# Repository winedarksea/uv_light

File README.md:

# uv_light
Licence: CERN Open Hardware Licence Version 2 - Strongly Reciprocal

 Custom Sun Lamp / Full Spectrum Lamp
 
 Background writeup [here](https://syllepsis.live/2024/12/31/light-for-health-and-a-custom-sun-lamp/)

A heatsink is important. All 16 leds are too much, unfortunately.

Problem: the comparator circuit for voltage sensing doesn't work properly, and needs a look at.

Minor problem: there's one trace that is bridged by the heatsink here. Using a non conductive thermal pad between the pcb and heatsink solves that problem, or redesign.

Recommendation: add a switch to the UV circuit as well. Also perhaps use larger switches than those specced here if you intend to switch the active lights often.

Designed for:
* QLUV07EYGE
* JE2835 3V N CLASS FAR RED
* Samsung LM302N White, Cool 6500K 
* Samsung LM302N WARM WHT 2700K 1212
* GT PSLR31.13-LUMQ-T1T2-1-150-R18 LED DURIS S5 GREEN 540NM SMD

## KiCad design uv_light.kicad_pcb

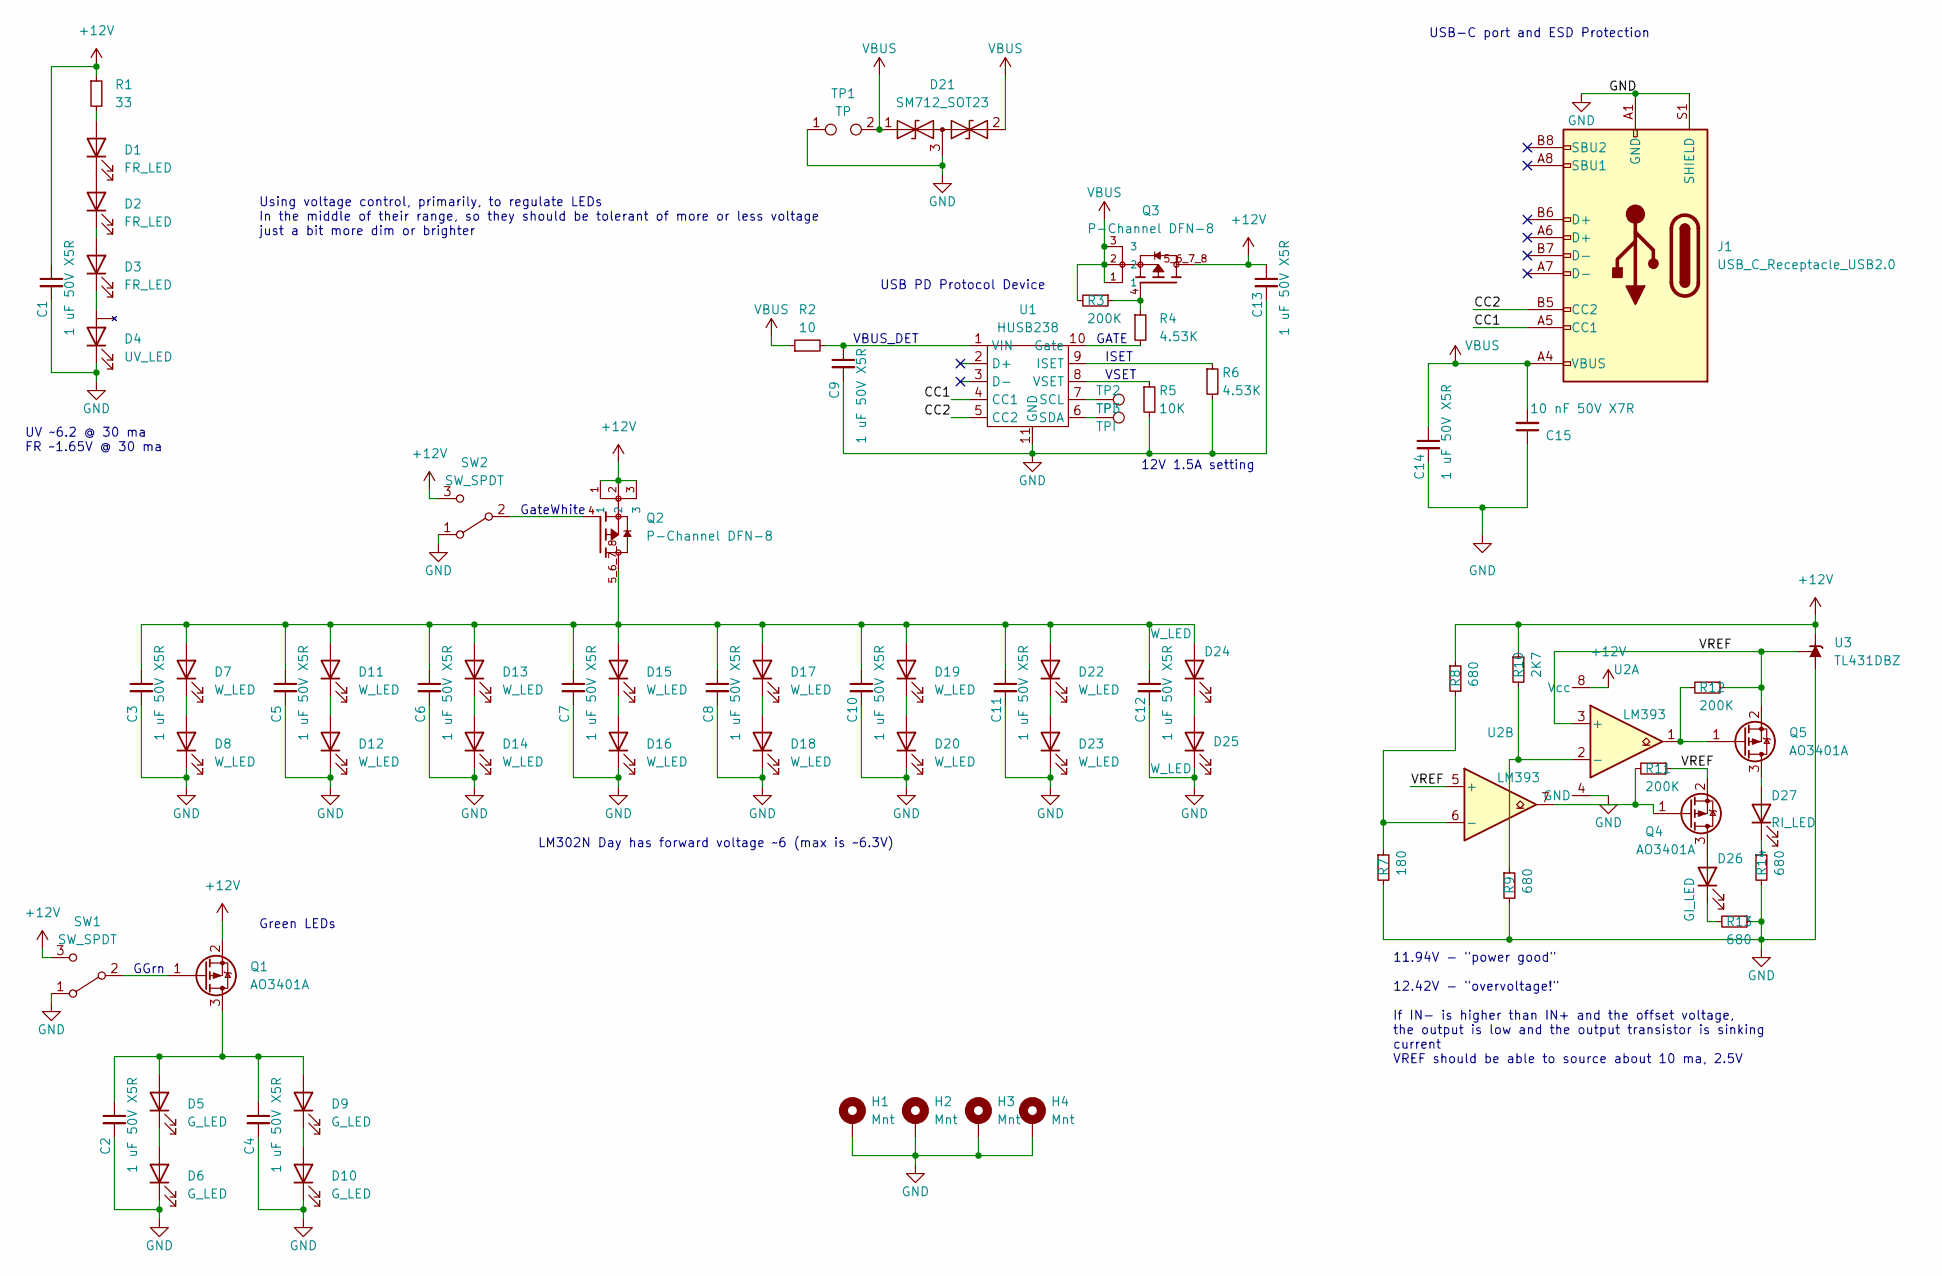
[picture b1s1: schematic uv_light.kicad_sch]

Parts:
C1, C2, C3, C4, C5, C6, C7, C8, C9, C10, C11, C12, C13, C14: 1 uF 50V X5R; C_0603_1608Metric
C15: 10 nF 50V X7R; C_0402_1005Metric_Pad0.74x0.62mm_HandSolder
D1, D2, D3: FR_LED; LED_PLCC_2835_Handsoldering
D4: UV_LED; LED_Cree-XHP35
D5, D6, D9, D10: G_LED; LED_SMD3030
D7, D8, D11, D12, D13, D14, D15, D16, D17, D18, D19, D20, D22, D23, D24, D25: W_LED; LED_SMD3030
D21: SM712_SOT23; SOT-23
D26: GI_LED; LED_0805_2012Metric_Pad1.15x1.40mm_HandSolder
D27: RI_LED; LED_0603_1608Metric_Pad1.05x0.95mm_HandSolder
H1, H2, H3, H4: Mnt; MountingHole_2.2mm_M2_DIN965_Pad
J1: USB_C_Receptacle_USB2.0; USB_C_Receptacle_HRO_TYPE-C-31-M-12
Q1, Q4, Q5: AO3401A; SOT-23
Q2, Q3: P-Channel DFN-8; TRANS_AONR21307
R1: 33; R_0603_1608Metric_Pad0.98x0.95mm_HandSolder
R2: 10; R_0805_2012Metric_Pad1.20x1.40mm_HandSolder
R3, R11, R12: 200K; R_0402_1005Metric_Pad0.72x0.64mm_HandSolder
R4, R6: 4.53K; R_0603_1608Metric_Pad0.98x0.95mm_HandSolder
R5: 10K; R_0603_1608Metric_Pad0.98x0.95mm_HandSolder
R7: 180; R_0603_1608Metric_Pad0.98x0.95mm_HandSolder
R8, R9, R13, R14: 680; R_0805_2012Metric_Pad1.20x1.40mm_HandSolder
R10: 2K7; R_0603_1608Metric_Pad0.98x0.95mm_HandSolder
SW1, SW2: SW_SPDT; SW_SPDT_PCM12
TP1: TP; TestPoint_2Pads_Pitch2.54mm_Drill0.8mm
TP2, TP3: TPI; TestPoint_Pad_D2.0mm
U1: HUSB238; DFN-10-1EP_3x3mm_P0.5mm_EP1.65x2.38mm
U2: LM393; SOIC-8_3.9x4.9mm_P1.27mm
U3: TL431DBZ; SOT-23

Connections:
+12V: C1.1, C13.1, Q1.2 (S), Q2.1, Q2.2, Q2.3, Q3.5_6_7_8, R1.1, R8.1, R10.1, SW1.3 (C), SW2.3 (C), U2.8 (Vcc), U3.1 (K)
/CC1: J1.A5 (CC1), U1.4 (CC1)
/CC2: J1.B5 (CC2), U1.5 (CC2)
/VREF: Q4.2 (S), Q5.2 (S), R11.1, R12.1, U2.3 (+), U2.5 (+), U3.2 (REF)
GND: C1.2, C2.2, C3.2, C4.2, C5.2, C6.2, C7.2, C8.2, C9.2, C10.2, C11.2, C12.2, C13.2, C14.2, C15.1, D4.1 (K), D6.1 (K), D8.1 (K), D10.1 (K), D12.1 (K), D14.1 (K), D16.1 (K), D18.1 (K), D20.1 (K), D21.3 (common), D23.1 (K), D25.1 (K), H1.1, H2.1, H3.1, H4.1, J1.A1 (GND), J1.A12 (GND), J1.B1 (GND), J1.B12 (GND), J1.S1 (SHIELD), R5.2, R6.2, R7.2, R9.2, R13.1, R14.2, SW1.1 (A), SW2.1 (A), TP1.1, U1.11 (GND), U2.4 (GND), U3.3 (A)
unnamed: D1.2 (A), R1.2
unnamed: D1.1 (K), D2.2 (A)
unnamed: D2.1 (K), D3.2 (A)
unnamed: D3.1 (K), D4.2 (A)
unnamed: C2.1, C4.1, D5.2 (A), D9.2 (A), Q1.3 (D)
unnamed: D5.1 (K), D6.2 (A)
unnamed: D7.1 (K), D8.2 (A)
unnamed: D9.1 (K), D10.2 (A)
unnamed: C3.1, C5.1, C6.1, C7.1, C8.1, C10.1, C11.1, C12.1, D7.2 (A), D11.2 (A), D13.2 (A), D15.2 (A), D17.2 (A), D19.2 (A), D22.2 (A), D24.2 (A), Q2.5_6_7_8
unnamed: D11.1 (K), D12.2 (A)
unnamed: D13.1 (K), D14.2 (A)
unnamed: D15.1 (K), D16.2 (A)
unnamed: D17.1 (K), D18.2 (A)
unnamed: D19.1 (K), D20.2 (A)
unnamed: D22.1 (K), D23.2 (A)
unnamed: D24.1 (K), D25.2 (A)
unnamed: D26.2 (A), Q4.3 (D)
unnamed: D26.1 (K), R13.2
unnamed: D27.2 (A), Q5.3 (D)
unnamed: D27.1 (K), R14.1
unnamed: Q1.1 (G), SW1.2 (B)
unnamed: Q3.4, R3.1, R4.1
unnamed: Q4.1 (G), R11.2, U2.7
unnamed: Q5.1 (G), R12.2, U2.1
unnamed: Q2.4, SW2.2 (B)
unnamed: R4.2, U1.10 (Gate)
unnamed: R6.1, U1.9 (ISET)
unnamed: TP2.1, U1.7 (SCL)
unnamed: TP3.1, U1.6 (SDA)
unnamed: C9.1, R2.2, U1.1 (VIN)
unnamed: R5.1, U1.8 (VSET)
unnamed: R9.1, R10.2, U2.2 (-)
unnamed: R7.1, R8.2, U2.6 (-)
VBUS: C14.1, C15.2, D21.1 (A1), D21.2 (A2), J1.A4 (VBUS), J1.A9 (VBUS), J1.B4 (VBUS), J1.B9 (VBUS), Q3.1, Q3.2, Q3.3, R2.1, R3.2, TP1.2

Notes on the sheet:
GateWhite
UV ~6.2 @ 30 ma FR ~1.65V @ 30 ma
12V 1.5A setting
Using voltage control, primarily, to regulate LEDs In the middle of their range, so they should be tolerant of more or less voltage just a bit more dim or brighter
11.94V - "power good" 12.42V - "overvoltage!" If IN- is higher than IN+ and the offset voltage, the output is low and the output transistor is sinking current VREF should be able to source about 10 ma, 2.5V
ISET
USB PD Protocol Device
Green LEDs
USB-C port and ESD Protection
GGrn
VBUS_DET
LM302N Day has forward voltage ~6 (max is ~6.3V)
VSET
GATE

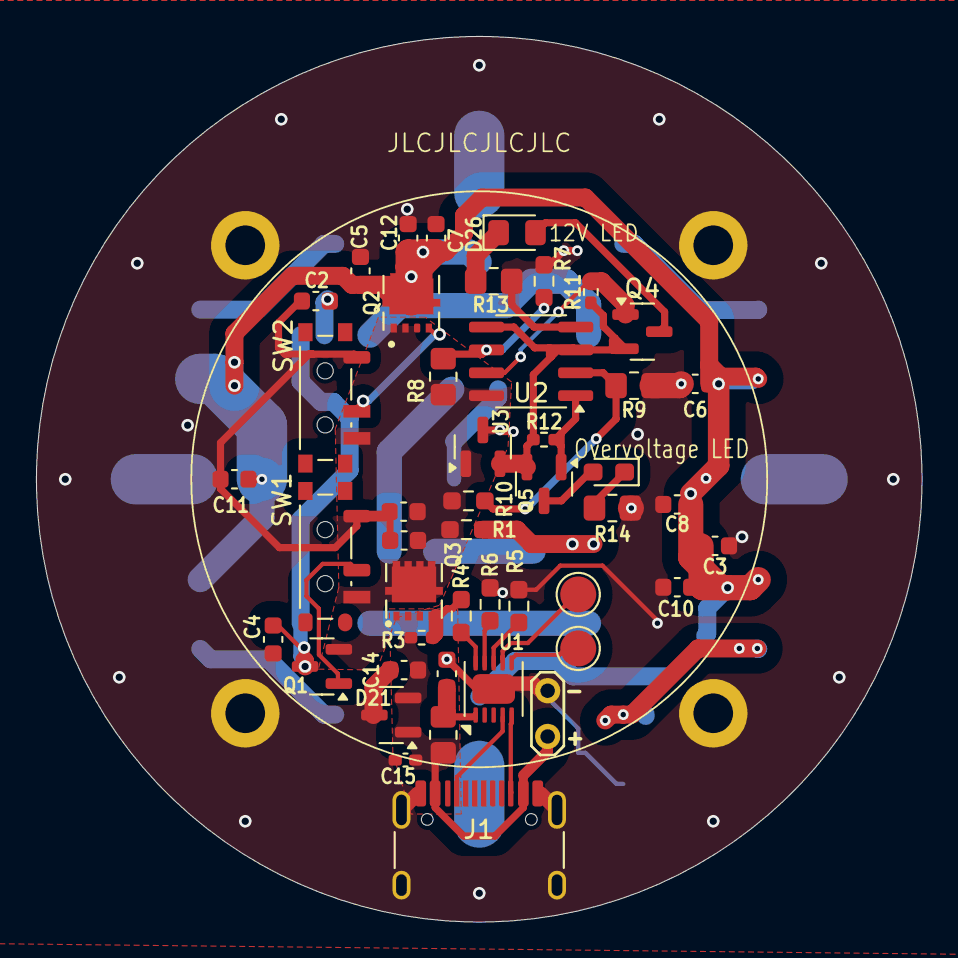
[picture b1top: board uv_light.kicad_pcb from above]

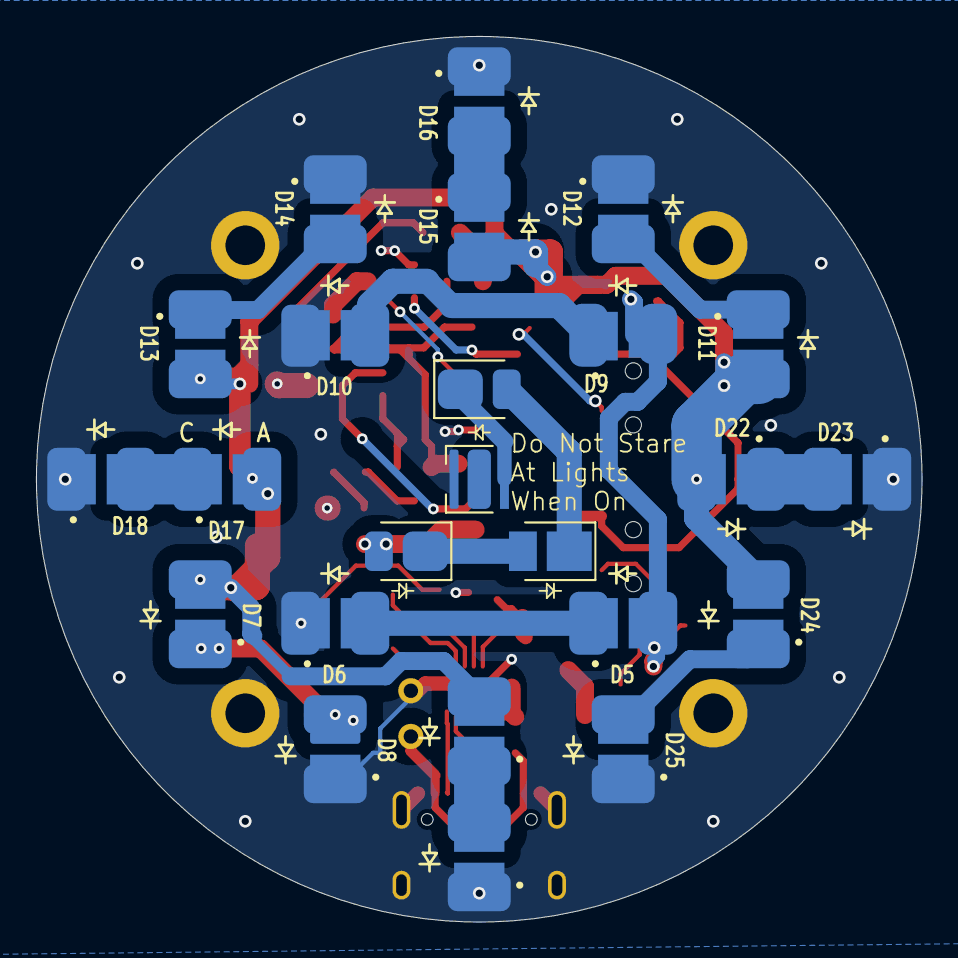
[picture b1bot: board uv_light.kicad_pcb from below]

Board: 2 copper layers, 49.2 x 49.2 mm, 74 parts (24 on the bottom side), 39 nets.

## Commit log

2024-12-31 add 3d files
2024-12-31 readme update
